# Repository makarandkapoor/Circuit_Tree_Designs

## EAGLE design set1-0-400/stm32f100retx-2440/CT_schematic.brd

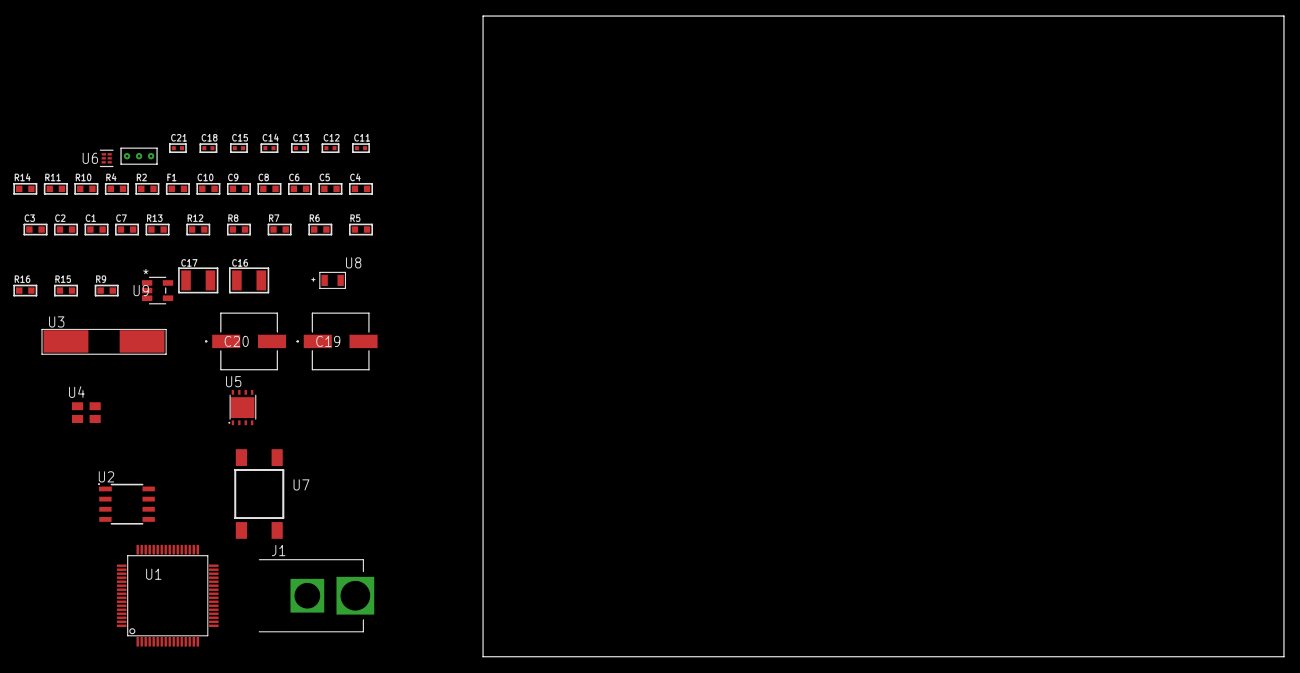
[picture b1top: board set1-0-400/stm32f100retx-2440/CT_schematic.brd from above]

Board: 2 copper layers, 100.0 x 80.0 mm, 47 parts (0 on the bottom side), 25 nets, no tracks yet.

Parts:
C1, C10: 1e-06; C0603
C2, C3, C4, C5, C6: 1e-07; C0603
C7: 4.7e-06; C0603
C8, C9: 1e-08; C0603
C11, C12: 1e-11; C0402
C13, C14, C15, C21: 1e-08; C0402
C16, C17: 1e-05; C1210
C18: 1e-07; C0402
C19, C20: 0.0001; EXV-9H
F1: 240.0; L0603
J1: PJ-037B; PJ-037B_PACKAGE
R2, R11: 1000.0; R0603
R4: 4700.0; R0603
R5, R6, R7, R8, R12, R13: 10000.0; R0603
R9: 100000.0; R0603
R10: 2231.0; R0603
R14: 9100.0; R0603
R15: 680000.0; R0603
R16: 120000.0; R0603
U1: stm32f100ret6; LQFP64
U2: AT25020B-SSHL-T; SOIC-8
U3: ABLS-25.000MHZ-B2F-T
U4: ASEK-32.768KHz-ECST; ASEK
U5: LP3878SDX-ADJ/NOPB; WSON-8
U6: TPS3895ADRYR; SON-6
U7: 4-1437565-2; SW_4-1437565-2
U8: Q65110A2395; LGM67K-G1J2-24-Z
U9: nc7sz125m5x; NC7SZ125M5X
U10: Dummy; DUMMY_PACKAGE_96

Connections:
CLK_CRYSTAL_U1_5: C11.1, U1.5, U3.1
CLK_CRYSTAL_U1_6: C12.1, U1.6, U3.2
CLK_U1_3: U1.3, U4.3
GND: C1.2, C2.2, C3.2, C4.2, C5.2, C6.2, C7.2, C8.2, C9.2, C10.2, C11.2, C12.2, C13.2, C14.2, C15.2, C16.2, C17.2, C18.2, C19.2, C20.2, C21.2, J1.2, R2.2, R5.2, R11.2, R14.2, R16.2, U1.12, U1.18, U1.31, U1.47, U1.63, U2.4, U4.2, U5.3, U5.PAD, U6.2, U8.C, U9.1, U9.3, U10.1
NET_U1_7: R4.1, U1.7, U9.4
NET_U1_13: C8.1, C9.1, C10.1, F1.1, U1.13
NET_U1_60: R5.1, U1.60
NET_U1_62: U7.3, U7.4
NET_U2_3: R6.1, U2.3
NET_U2_7: R8.1, U2.7
NET_U5_1: C15.1, U5.1
NET_U5_6: R10.2, R11.1, U5.6
NET_U5_8: R9.1, U5.8
NET_U6_1: R13.1, R14.1, U6.1
NET_U6_3: R15.2, R16.1, U6.3
NET_U6_4: R12.1, U6.4, U9.2
NET_U7_1: R2.1, U7.1, U7.2
PROC_ADC1_IN0: U1.14, U10.2
PROC_ADC1_IN1: U1.15, U10.3
PROC_SPI1_MISO: U1.22, U2.2
PROC_SPI1_MOSI: U1.23, U2.5
PROC_SPI1_NSS: R7.1, U1.20, U2.1
PROC_SPI1_SCK: U1.21, U2.6
VCC_S1_14V8: C16.1, C19.1, C20.1, J1.1, R9.2, U5.4
VCC_TIER1_3V3: C1.1, C2.1, C3.1, C4.1, C5.1, C6.1, C7.1, C13.1, C14.1, C17.1, C18.1, C21.1, F1.2, R4.2, R6.2, R7.2, R8.2, R10.1, R12.2, R13.2, R15.1, U1.1, U1.19, U1.32, U1.48, U1.64, U2.8, U4.4, U5.5, U6.6, U9.5

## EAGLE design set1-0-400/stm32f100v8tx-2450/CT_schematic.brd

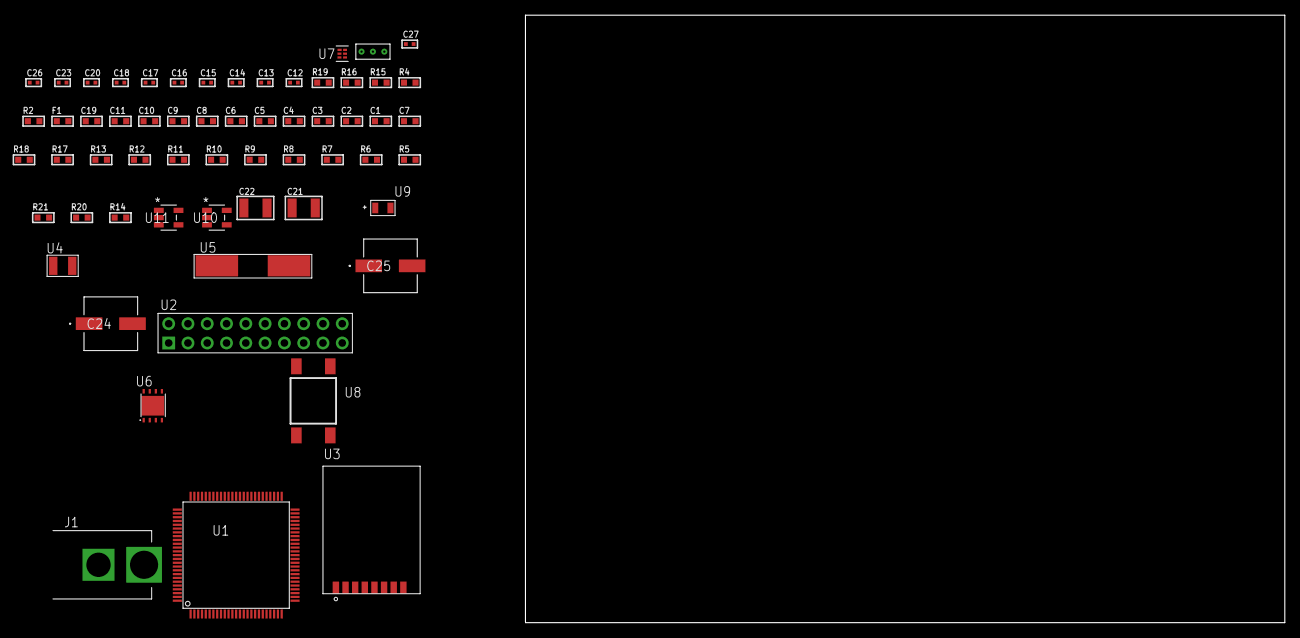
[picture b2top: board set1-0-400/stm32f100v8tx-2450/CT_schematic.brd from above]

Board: 2 copper layers, 100.0 x 80.0 mm, 60 parts (0 on the bottom side), 29 nets, no tracks yet.

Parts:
C1, C11, C19: 1e-06; C0603
C2, C3, C4, C5, C6, C8: 1e-07; C0603
C7: 4.7e-06; C0603
C9, C10: 1e-08; C0603
C12, C13, C14, C15: 1e-11; C0402
C16, C17, C18, C23: 1e-07; C0402
C20, C26, C27: 1e-08; C0402
C21, C22: 1e-05; C1210
C24, C25: 0.0001; EXV-9H
F1: 240.0; L0603
J1: PJ-037B; PJ-037B_PACKAGE
R2, R16: 1000.0; R0603
R4: 4700.0; R0603
R5, R6, R7, R8, R9, R10, R11, R12, R13, R17, R18: 10000.0; R0603
R14: 100000.0; R0603
R15: 2231.0; R0603
R19: 9100.0; R0603
R20: 680000.0; R0603
R21: 120000.0; R0603
U1: stm32f100v8t7; LQFP100
U2: TST-110-05-T-D-RA
U3: RFM75-S
U4: ABS07-32.768KHZ-7-T
U5: ABLS-25.000MHZ-B2F-T
U6: LP3878SDX-ADJ/NOPB; WSON-8
U7: TPS3895ADRYR; SON-6
U8: 4-1437565-2; SW_4-1437565-2
U9: Q65110A2395; LGM67K-G1J2-24-Z
U10, U11: nc7sz125m5x; NC7SZ125M5X
U12: Dummy; DUMMY_PACKAGE_125

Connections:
CLK_CRYSTAL_U1_8: C12.1, U1.8, U4.1
CLK_CRYSTAL_U1_9: C13.1, U1.9, U4.2
CLK_CRYSTAL_U1_12: C14.1, U1.12, U5.1
CLK_CRYSTAL_U1_13: C15.1, U1.13, U5.2
GND: C1.2, C2.2, C3.2, C4.2, C5.2, C6.2, C7.2, C8.2, C9.2, C10.2, C11.2, C12.2, C13.2, C14.2, C15.2, C16.2, C17.2, C18.2, C19.2, C20.2, C21.2, C22.2, C23.2, C24.2, C25.2, C26.2, C27.2, J1.2, R2.2, R5.2, R11.2, R16.2, R19.2, R21.2, U1.10, U1.19, U1.20, U1.27, U1.49, U1.74, U1.99, U2.4, U2.6, U2.8, U2.10, U2.12, U2.14, U2.16, U2.18, U2.20, U3.1, U6.3, U6.PAD, U7.2, U9.C, U10.2, U10.3, U11.1, U11.3, U12.1
NET_U1_14: R4.1, U1.14, U11.4
NET_U1_22: C9.1, C10.1, C11.1, F1.1, U1.21, U1.22
NET_U1_94: R5.1, U1.94
NET_U1_98: U8.3, U8.4
NET_U2_3: R6.1, U2.3
NET_U2_7: R8.1, U2.7
NET_U2_9: R9.1, U2.9
NET_U2_19: R11.1, U2.19
NET_U3_3: R12.1, U3.3
NET_U6_1: C20.1, U6.1
NET_U6_6: R15.2, R16.1, U6.6
NET_U6_8: R14.1, U6.8
NET_U7_1: R18.1, R19.1, U7.1
NET_U7_3: R20.2, R21.1, U7.3
NET_U7_4: R17.1, U7.4, U10.4, U11.2
NET_U8_1: R2.1, U8.1, U8.2
PROC_PE2: U1.1, U12.2
PROC_PE3: U1.2, U12.3
PROC_SPI1_NSS: R13.1, U3.4
PROC_SYS_JTDI: R7.1, U1.77, U2.5
PROC_SYS_JTDO_TRACESWO: U1.89, U2.13
RST_OUT_U2_SRESET_B: R10.1, U2.15, U10.1
VCC_S1_14V3: C21.1, C24.1, C25.1, J1.1, R14.2, U6.4
VCC_TIER1_3V3: C1.1, C2.1, C3.1, C4.1, C5.1, C6.1, C7.1, C8.1, C16.1, C17.1, C18.1, C19.1, C22.1, C23.1, C26.1, C27.1, F1.2, R4.2, R6.2, R7.2, R8.2, R9.2, R10.2, R12.2, R13.2, R15.1, R17.2, R18.2, R20.1, U1.6, U1.11, U1.28, U1.50, U1.75, U1.100, U2.1, U2.2, U3.2, U6.5, U7.6, U10.5, U11.5

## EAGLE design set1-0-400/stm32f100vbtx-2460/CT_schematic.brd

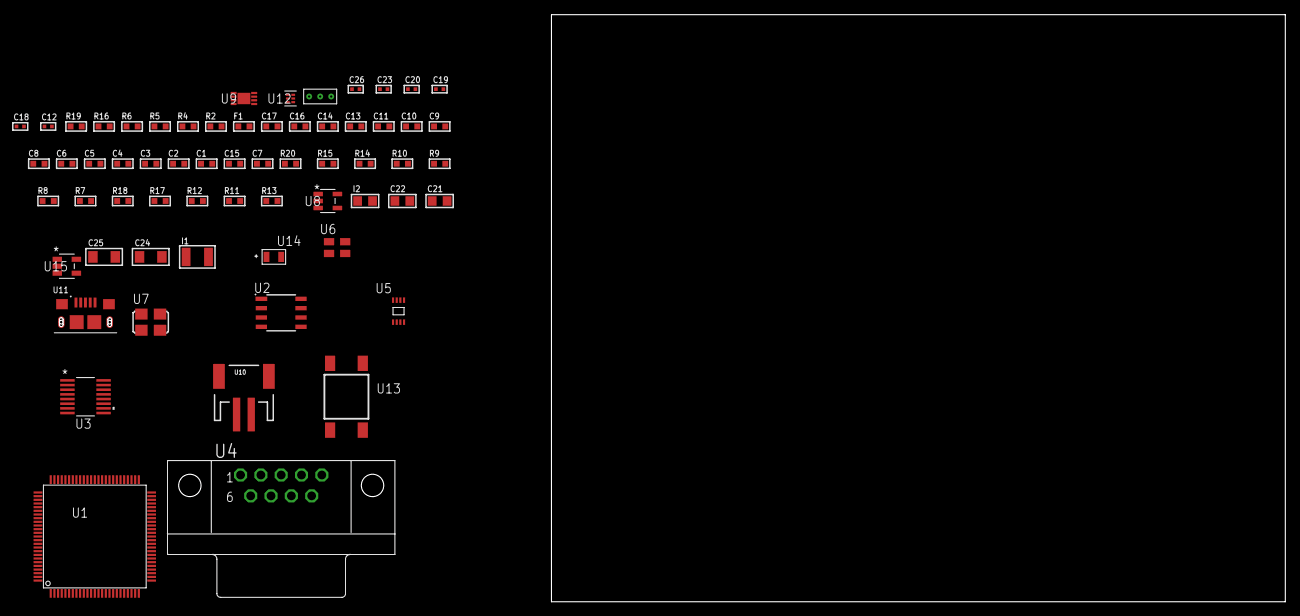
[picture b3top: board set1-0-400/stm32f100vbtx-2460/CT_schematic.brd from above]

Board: 2 copper layers, 167.1 x 80.0 mm, 63 parts (0 on the bottom side), 42 nets, no tracks yet.

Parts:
C1, C11, C13, C14, C16, C17: 1e-06; C0603
C2, C3, C4, C5, C6, C8: 1e-07; C0603
C7: 4.7e-06; C0603
C9, C10: 1e-08; C0603
C12, C18, C19, C20, C26: 1e-08; C0402
C15: 2.2e-07; C0603
C21, C22: 1e-05; C0805
C23: 1e-07; C0402
C24, C25: 1e-05; C1206
F1: 240.0; L0603
I1: 1e-05; L1210
I2: 2.2e-06; L0805
R2: 1000.0; R0603
R4: 4700.0; R0603
R5, R6: 2200.0; R0603
R7, R8, R9, R10, R14, R15, R20: 10000.0; R0603
R11: 100000.0; R0603
R12: 220000.0; R0603
R13: 1000000.0; R0603
R16: 9100.0; R0603
R17: 680000.0; R0603
R18: 120000.0; R0603
R19: 2000.0; R0603
U1: stm32f100vbt7; LQFP100
U2: AT25M02-SSHD-T; SOIC-8
U3: LTC2804CGN-1#PBF; SSOP-16
U4: 182-009-113R531; 182-009-MALE
U5: 24AA16-I/MC; TDFN-8/6MM
U6: ASEK-32.768KHz-ECST; ASEK
U7: ASFL1-25MHZ-NCS; ASFL1
U8: ltc3406es5; TSOT-23-5
U9: MCP73831T-2ACI/MC; DFN8_2X3MC
U10: S2B-PH-SM4-TB(LF)(SN); JST-2-SMD
U11: 10118193-0001LF; FCI_10118193-0001LF
U12: TPS3895ADRYR; SON-6
U13: 4-1437565-2; SW_4-1437565-2
U14: Q65110A2395; LGM67K-G1J2-24-Z
U15: nc7sz125m5x; NC7SZ125M5X
U16: Dummy; DUMMY_PACKAGE_140

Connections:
CLK_U1_8: U1.8, U6.3
CLK_U1_12: U1.12, U7.3
GND: C1.2, C2.2, C3.2, C4.2, C5.2, C6.2, C7.2, C8.2, C9.2, C10.2, C11.2, C12.2, C13.2, C14.2, C16.2, C17.2, C18.2, C19.2, C20.2, C21.2, C22.1, C22.2, C23.2, C24.2, C25.2, C26.2, R2.2, R7.2, R12.2, R16.2, R18.2, R19.2, U1.10, U1.19, U1.20, U1.27, U1.49, U1.74, U1.99, U2.4, U3.8, U4.5, U5.4, U6.2, U7.2, U8.2, U9.6, U9.9, U10.2, U11.5, U11.6, U11.7, U11.8, U11.9, U12.2, U14.C, U15.1, U15.3, U16.1
INPUT_USBPOWER_5V: C24.1, R20.2, U9.1, U9.2, U11.1
NET_U1_14: R4.1, U1.14, U15.4
NET_U1_22: C9.1, C10.1, C11.1, F1.1, U1.21, U1.22
NET_U1_92: R5.1, U1.92, U5.6
NET_U1_93: R6.1, U1.93, U5.5
NET_U1_94: R7.1, U1.94
NET_U1_98: U13.3, U13.4
NET_U2_3: R8.1, U2.3
NET_U2_7: R10.1, U2.7
NET_U3_6: C13.1, U3.6
NET_U3_7: C15.1, I1.2, U3.7
NET_U3_9: C14.1, U3.9
NET_U3_10: C15.2, U3.10
NET_U3_11: R11.1, U3.11
NET_U4_2: U3.1, U4.2
NET_U4_3: U3.3, U4.3
NET_U4_7: U3.2, U4.7
NET_U4_8: U3.4, U4.8
NET_U8_3: I2.1, U8.3
NET_U8_5: R12.1, R13.1, U8.5
NET_U8_ATNET_3: I2.2, R13.2
NET_U9_5: R20.1, U9.5
NET_U9_8: R19.1, U9.8
NET_U12_1: R15.1, R16.1, U12.1
NET_U12_3: R17.2, R18.1, U12.3
NET_U12_4: R14.1, U12.4, U15.2
NET_U13_1: R2.1, U13.1, U13.2
PROC_ADC1_IN0: U1.23, U16.2
PROC_ADC1_IN1: U1.24, U16.3
PROC_SPI1_MISO: U1.31, U2.2
PROC_SPI1_MOSI: U1.32, U2.5
PROC_SPI1_NSS: R9.1, U1.29, U2.1
PROC_SPI1_SCK: U1.30, U2.6
PROC_USART1_CTS: U1.70, U3.13
PROC_USART1_RTS: U1.71, U3.15
PROC_USART1_RX: U1.69, U3.16
PROC_USART1_TX: U1.68, U3.14
VCC_S1_3V7: C21.1, C25.1, U8.4, U9.3, U9.4, U10.1
VCC_TIER1_3V3: C1.1, C2.1, C3.1, C4.1, C5.1, C6.1, C7.1, C8.1, C12.1, C16.1, C17.1, C18.1, C19.1, C20.1, C22.2, C23.1, C26.1, F1.2, I1.1, I2.2, R4.2, R5.2, R6.2, R8.2, R9.2, R10.2, R11.2, R13.2, R14.2, R15.2, R17.1, U1.6, U1.11, U1.28, U1.50, U1.75, U1.100, U2.8, U3.5, U3.12, U5.7, U5.8, U6.4, U7.4, U12.6, U15.5

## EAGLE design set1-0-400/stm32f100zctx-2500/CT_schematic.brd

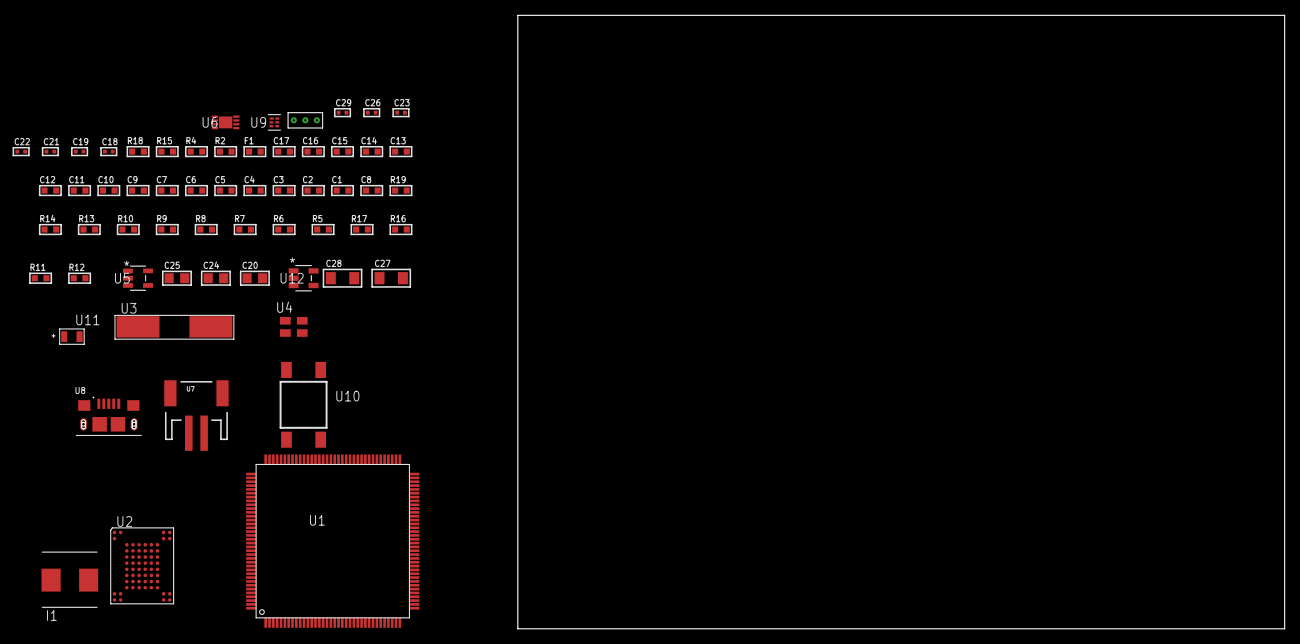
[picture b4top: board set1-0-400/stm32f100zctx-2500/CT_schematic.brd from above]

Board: 2 copper layers, 156.9 x 80.0 mm, 61 parts (0 on the bottom side), 35 nets, no tracks yet.

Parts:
C1, C17: 1e-06; C0603
C2, C3, C4, C5, C6, C7, C9, C10, C11, C12, C13, C14: 1e-07; C0603
C8: 4.7e-06; C0603
C15, C16: 1e-08; C0603
C18, C19: 1e-11; C0402
C20, C24, C25: 1e-05; C0805
C21, C22, C26: 1e-07; C0402
C23, C29: 1e-08; C0402
C27, C28: 1e-05; C1206
F1: 240.0; L0603
I1: 2e-06; WE-HCI_7030/7040/7050
R2: 1000.0; R0603
R4: 4700.0; R0603
R5, R6, R7, R8, R9, R10, R13, R14, R19: 10000.0; R0603
R11: 220000.0; R0603
R12: 1000000.0; R0603
R15: 9100.0; R0603
R16: 680000.0; R0603
R17: 120000.0; R0603
R18: 2000.0; R0603
U1: stm32f100zct7; LQFP144
U2: TH58NVG3S0HBAI4
U3: ABLS-25.000MHZ-B2F-T
U4: ASEK-32.768KHz-ECST; ASEK
U5: ltc3406es5; TSOT-23-5
U6: MCP73831T-2ACI/MC; DFN8_2X3MC
U7: S2B-PH-SM4-TB(LF)(SN); JST-2-SMD
U8: 10118193-0001LF; FCI_10118193-0001LF
U9: TPS3895ADRYR; SON-6
U10: 4-1437565-2; SW_4-1437565-2
U11: Q65110A2395; LGM67K-G1J2-24-Z
U12: nc7sz125m5x; NC7SZ125M5X
U13: Dummy; DUMMY_PACKAGE_128

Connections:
CLK_CRYSTAL_U1_23: C18.1, U1.23, U3.1
CLK_CRYSTAL_U1_24: C19.1, U1.24, U3.2
CLK_U1_8: U1.8, U4.3
GND: C1.2, C2.2, C3.2, C4.2, C5.2, C6.2, C7.2, C8.2, C9.2, C10.2, C11.2, C12.2, C13.2, C14.2, C15.2, C16.2, C17.2, C18.2, C19.2, C20.2, C21.2, C22.2, C23.2, C24.2, C25.1, C25.2, C26.2, C27.2, C28.2, C29.2, R2.2, R5.2, R11.2, R15.2, R17.2, R18.2, U1.16, U1.30, U1.31, U1.38, U1.51, U1.61, U1.71, U1.83, U1.94, U1.107, U1.120, U1.130, U1.143, U2.C5, U2.K3, U2.K8, U4.2, U5.2, U6.6, U6.9, U7.2, U8.5, U8.6, U8.7, U8.8, U8.9, U9.2, U11.C, U12.1, U12.3, U13.1
INPUT_USBPOWER_5V: C27.1, R19.2, U6.1, U6.2, U8.1
NET_U1_25: R4.1, U1.25, U12.4
NET_U1_33: C15.1, C16.1, C17.1, F1.1, U1.32, U1.33
NET_U1_138: R5.1, U1.138
NET_U1_142: U10.3, U10.4
NET_U2_C3: R9.1, U2.C3
NET_U2_C6: R6.1, U2.C6
NET_U2_C8: R10.1, U2.C8
NET_U5_3: I1.1, U5.3
NET_U5_5: R11.1, R12.1, U5.5
NET_U5_ATNET_3: I1.2, R12.2
NET_U6_5: R19.1, U6.5
NET_U6_8: R18.1, U6.8
NET_U9_1: R14.1, R15.1, U9.1
NET_U9_3: R16.2, R17.1, U9.3
NET_U9_4: R13.1, U9.4, U12.2
NET_U10_1: R2.1, U10.1, U10.2
PROC_ADC1_IN0: U1.34, U13.2
PROC_ADC1_IN1: U1.35, U13.3
PROC_FSMC_D0: U1.85, U2.H4
PROC_FSMC_D1: U1.86, U2.J4
PROC_FSMC_D2: U1.114, U2.K4
PROC_FSMC_D3: U1.115, U2.K5
PROC_FSMC_D4: U1.58, U2.K6
PROC_FSMC_D5: U1.59, U2.J7
PROC_FSMC_D6: U1.60, U2.K7
PROC_FSMC_D7: U1.63, U2.J8
PROC_FSMC_NOE: R7.1, U1.118, U2.D4
PROC_FSMC_NWE: R8.1, U1.119, U2.C7
VCC_S1_3V7: C24.1, C28.1, U5.4, U6.3, U6.4, U7.1
VCC_TIER1_3V3: C1.1, C2.1, C3.1, C4.1, C5.1, C6.1, C7.1, C8.1, C9.1, C10.1, C11.1, C12.1, C13.1, C14.1, C20.1, C21.1, C22.1, C23.1, C25.2, C26.1, C29.1, F1.2, I1.2, R4.2, R6.2, R7.2, R8.2, R9.2, R10.2, R12.2, R13.2, R14.2, R16.1, U1.6, U1.17, U1.39, U1.52, U1.62, U1.72, U1.84, U1.95, U1.108, U1.121, U1.131, U1.144, U2.H8, U2.J6, U4.4, U9.6, U12.5

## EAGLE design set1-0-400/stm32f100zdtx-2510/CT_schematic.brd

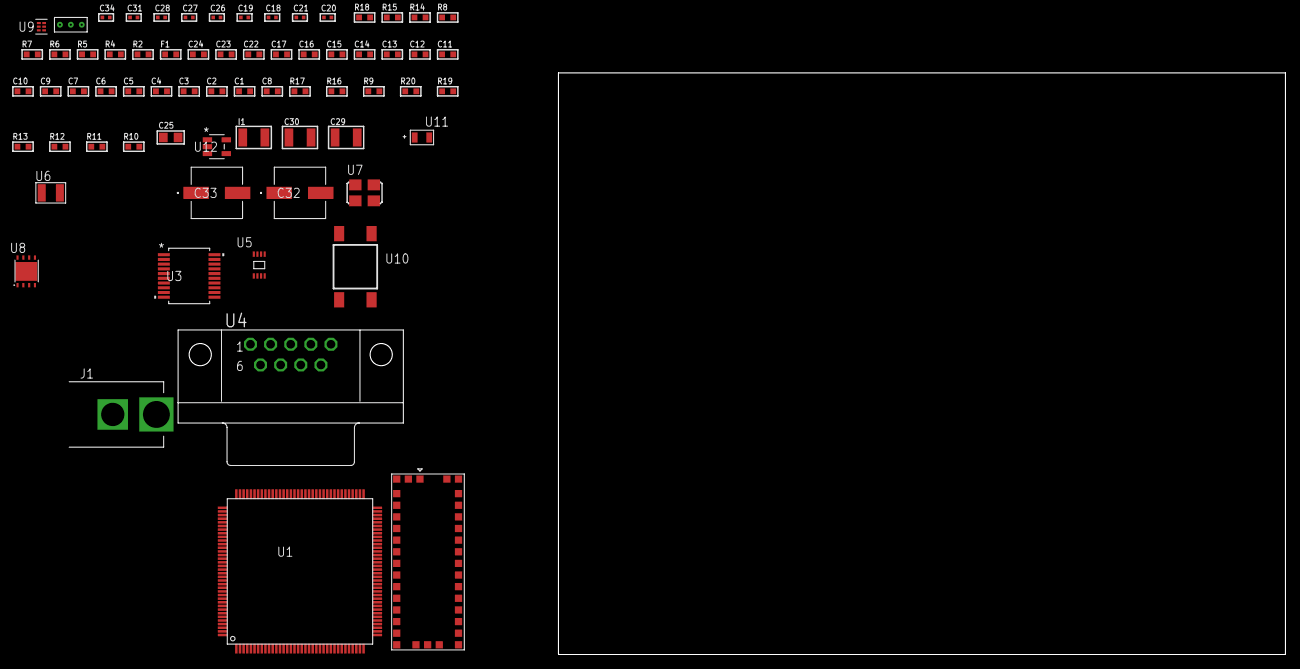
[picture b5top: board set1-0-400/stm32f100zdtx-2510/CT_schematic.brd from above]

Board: 2 copper layers, 100.0 x 80.0 mm, 68 parts (0 on the bottom side), 37 nets, no tracks yet.

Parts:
C1, C17, C22, C23, C24: 1e-06; C0603
C2, C3, C4, C5, C6, C7, C9, C10, C11, C12, C13, C14: 1e-07; C0603
C8: 4.7e-06; C0603
C15, C16: 1e-08; C0603
C18, C19: 1e-11; C0402
C20, C21: 2.2e-11; C0402
C25: 4.7e-06; C0805
C26, C27, C28, C34: 1e-08; C0402
C29, C30: 1e-05; C1210
C31: 1e-07; C0402
C32, C33: 0.0001; EXV-9H
F1: 240.0; L0603
I1: 1.5e-05; L1210
J1: PJ-037B; PJ-037B_PACKAGE
R2, R15: 1000.0; R0603
R4: 4700.0; R0603
R5, R6, R7, R8: 2200.0; R0603
R9, R16, R17: 10000.0; R0603
R10, R11, R12, R13: 100000.0; R0603
R14: 2231.0; R0603
R18: 9100.0; R0603
R19: 680000.0; R0603
R20: 120000.0; R0603
U1: stm32f100zdt7; LQFP144
U2: M10382
U3: MAX3218EAP+T; SSOP-20
U4: 182-009-113R531; 182-009-MALE
U5: 24AA16-I/MC; TDFN-8/6MM
U6: ABS07-32.768KHZ-7-T
U7: ASFL1-25MHZ-NCS; ASFL1
U8: LP3878SDX-ADJ/NOPB; WSON-8
U9: TPS3895ADRYR; SON-6
U10: 4-1437565-2; SW_4-1437565-2
U11: Q65110A2395; LGM67K-G1J2-24-Z
U12: nc7sz125m5x; NC7SZ125M5X
U13: Dummy; DUMMY_PACKAGE_145

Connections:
CLK_CRYSTAL_U1_8: C18.1, U1.8, U6.1
CLK_CRYSTAL_U1_9: C19.1, U1.9, U6.2
CLK_U1_23: U1.23, U7.3
GND: C1.2, C2.2, C3.2, C4.2, C5.2, C6.2, C7.2, C8.2, C9.2, C10.2, C11.2, C12.2, C13.2, C14.2, C15.2, C16.2, C17.2, C18.2, C19.2, C20.2, C21.2, C22.2, C23.2, C24.2, C26.2, C27.2, C28.2, C29.2, C30.2, C31.2, C32.2, C33.2, C34.2, J1.2, R2.2, R9.2, R15.2, R18.2, R20.2, U1.16, U1.30, U1.31, U1.38, U1.51, U1.61, U1.71, U1.83, U1.94, U1.107, U1.120, U1.130, U1.143, U2.2, U2.4, U2.14, U2.17, U2.21, U2.24, U2.26, U2.28, U2.33, U2.34, U2.35, U2.36, U3.5, U3.17, U3.20, U4.5, U5.4, U7.2, U8.3, U8.PAD, U9.2, U11.C, U12.1, U12.3, U13.1
NET_U1_25: R4.1, U1.25, U12.4
NET_U1_33: C15.1, C16.1, C17.1, F1.1, U1.32, U1.33
NET_U1_69: R7.1, U1.69, U5.6
NET_U1_70: R8.1, U1.70, U5.5
NET_U1_136: R5.1, U1.136, U2.19
NET_U1_137: R6.1, U1.137, U2.18
NET_U1_138: R9.1, U1.138
NET_U1_142: U10.3, U10.4
NET_U3_1: I1.1, U3.1
NET_U3_2: R10.1, U3.2
NET_U3_3: R11.1, U3.3
NET_U3_4: R12.1, U3.4
NET_U3_15: C24.1, U3.15
NET_U3_16: C25.2, U3.16
NET_U3_18: C25.1, U3.18
NET_U3_19: C23.1, U3.19
NET_U4_2: U3.12, U4.2
NET_U4_3: U3.14, U4.3
NET_U4_7: U3.11, U4.7
NET_U4_8: U3.13, U4.8
NET_U8_1: C28.1, U8.1
NET_U8_6: R14.2, R15.1, U8.6
NET_U8_8: R13.1, U8.8
NET_U9_1: R17.1, R18.1, U9.1
NET_U9_3: R19.2, R20.1, U9.3
NET_U9_4: R16.1, U9.4, U12.2
NET_U10_1: R2.1, U10.1, U10.2
PROC_ADC1_IN0: U1.34, U13.2
PROC_ADC1_IN1: U1.35, U13.3
PROC_UART4_RX: U1.112, U3.9
PROC_UART4_TX: U1.111, U3.7
VCC_S1_11V6: C29.1, C32.1, C33.1, J1.1, R13.2, U8.4
VCC_TIER1_3V3: C1.1, C2.1, C3.1, C4.1, C5.1, C6.1, C7.1, C8.1, C9.1, C10.1, C11.1, C12.1, C13.1, C14.1, C20.1, C21.1, C22.1, C26.1, C27.1, C30.1, C31.1, C34.1, F1.2, I1.2, R4.2, R5.2, R6.2, R7.2, R8.2, R10.2, R11.2, R12.2, R14.1, R16.2, R17.2, R19.1, U1.6, U1.17, U1.39, U1.52, U1.62, U1.72, U1.84, U1.95, U1.108, U1.121, U1.131, U1.144, U2.5, U2.25, U2.27, U3.6, U5.7, U5.8, U7.4, U8.5, U9.6, U12.5

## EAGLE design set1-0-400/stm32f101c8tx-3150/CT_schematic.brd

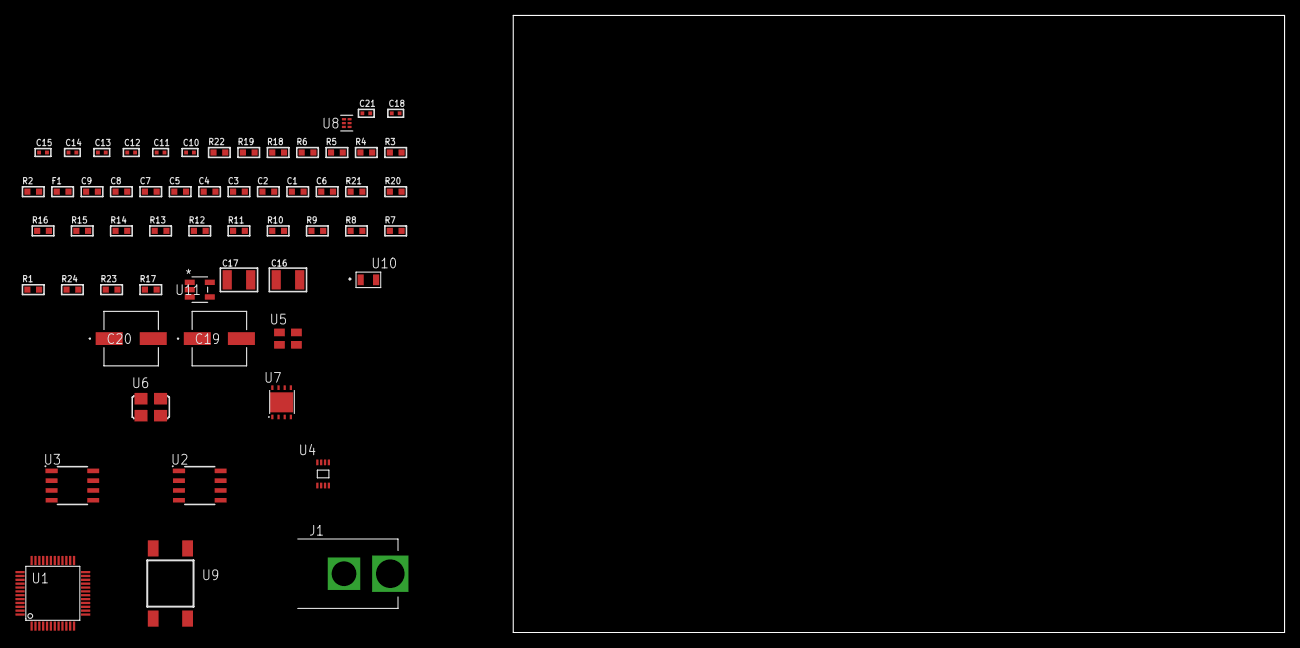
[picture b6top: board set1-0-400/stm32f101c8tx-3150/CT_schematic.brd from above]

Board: 2 copper layers, 100.0 x 80.0 mm, 58 parts (0 on the bottom side), 34 nets, no tracks yet.

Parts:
C1, C9: 1e-06; C0603
C2, C3, C4, C5: 1e-07; C0603
C6: 4.7e-06; C0603
C7, C8: 1e-08; C0603
C10, C11, C12, C13, C14, C15, C21: 1e-08; C0402
C16, C17: 1e-05; C1210
C18: 1e-07; C0402
C19, C20: 0.0001; EXV-9H
F1: 240.0; L0603
J1: PJ-037B; PJ-037B_PACKAGE
R1, R7, R8, R9, R10, R11, R12, R13, R14, R15, R16, R20, R21: 10000.0; R0603
R2, R19: 1000.0; R0603
R3: 1600.5; R0603
R4: 4700.0; R0603
R5, R6: 2200.0; R0603
R17: 100000.0; R0603
R18: 2231.0; R0603
R22: 9100.0; R0603
R23: 680000.0; R0603
R24: 120000.0; R0603
U1: STM32F101C8T6; LQFP48
U2: AT25080B-SSHL-T; SOIC-8
U3: AT25M01-SSHM-T; SOIC-8
U4: 24AA128T-I/MNY; TDFN-8/6MM
U5: ASEK-32.768KHz-ECST; ASEK
U6: ASFL1-25MHZ-NCS; ASFL1
U7: LP3878SDX-ADJ/NOPB; WSON-8
U8: TPS3895ADRYR; SON-6
U9: 4-1437565-2; SW_4-1437565-2
U10: Q65110A2395; LGM67K-G1J2-24-Z
U11: nc7sz125m5x; NC7SZ125M5X

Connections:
CLK_U1_3: U1.3, U5.3
CLK_U1_5: U1.5, U6.3
GND: C1.2, C2.2, C3.2, C4.2, C5.2, C6.2, C7.2, C8.2, C9.2, C10.2, C11.2, C12.2, C13.2, C14.2, C15.2, C16.2, C17.2, C18.2, C19.2, C20.2, C21.2, J1.2, R2.2, R7.2, R14.2, R16.2, R19.2, R22.2, R24.2, U1.8, U1.23, U1.35, U1.47, U2.4, U3.4, U4.4, U5.2, U6.2, U7.3, U7.PAD, U8.2, U10.C, U11.1, U11.3
NET_U1_7: R4.1, U1.7, U11.4
NET_U1_9: C7.1, C8.1, C9.1, F1.1, U1.9
NET_U1_42: R5.1, U1.42, U4.6
NET_U1_43: R6.1, U1.43, U4.5
NET_U1_44: R7.1, U1.44
NET_U1_45: R3.1, U1.45, U10.A
NET_U1_46: R1.1, U1.46, U9.3, U9.4
NET_U2_3: R8.1, U2.3
NET_U2_7: R10.1, U2.7
NET_U3_3: R11.1, U3.3
NET_U3_7: R13.1, U3.7
NET_U4_1: R14.1, U4.1
NET_U4_2: R15.1, U4.2
NET_U4_3: R16.1, U4.3
NET_U7_1: C15.1, U7.1
NET_U7_6: R18.2, R19.1, U7.6
NET_U7_8: R17.1, U7.8
NET_U8_1: R21.1, R22.1, U8.1
NET_U8_3: R23.2, R24.1, U8.3
NET_U8_4: R20.1, U8.4, U11.2
NET_U9_1: R2.1, U9.1, U9.2
PROC_SPI1_MISO: U1.16, U2.2
PROC_SPI1_MOSI: U1.17, U2.5
PROC_SPI1_NSS: R9.1, U1.14, U2.1
PROC_SPI1_SCK: U1.15, U2.6
PROC_SPI2_MISO: U1.27, U3.2
PROC_SPI2_MOSI: U1.28, U3.5
PROC_SPI2_NSS: R12.1, U1.25, U3.1
PROC_SPI2_SCK: U1.26, U3.6
VCC_S1_15V0: C16.1, C19.1, C20.1, J1.1, R17.2, U7.4
VCC_TIER1_3V3: C1.1, C2.1, C3.1, C4.1, C5.1, C6.1, C10.1, C11.1, C12.1, C13.1, C14.1, C17.1, C18.1, C21.1, F1.2, R1.2, R3.2, R4.2, R5.2, R6.2, R8.2, R9.2, R10.2, R11.2, R12.2, R13.2, R15.2, R18.1, R20.2, R21.2, R23.1, U1.1, U1.24, U1.36, U1.48, U2.8, U3.8, U4.7, U4.8, U5.4, U6.4, U7.5, U8.6, U11.5

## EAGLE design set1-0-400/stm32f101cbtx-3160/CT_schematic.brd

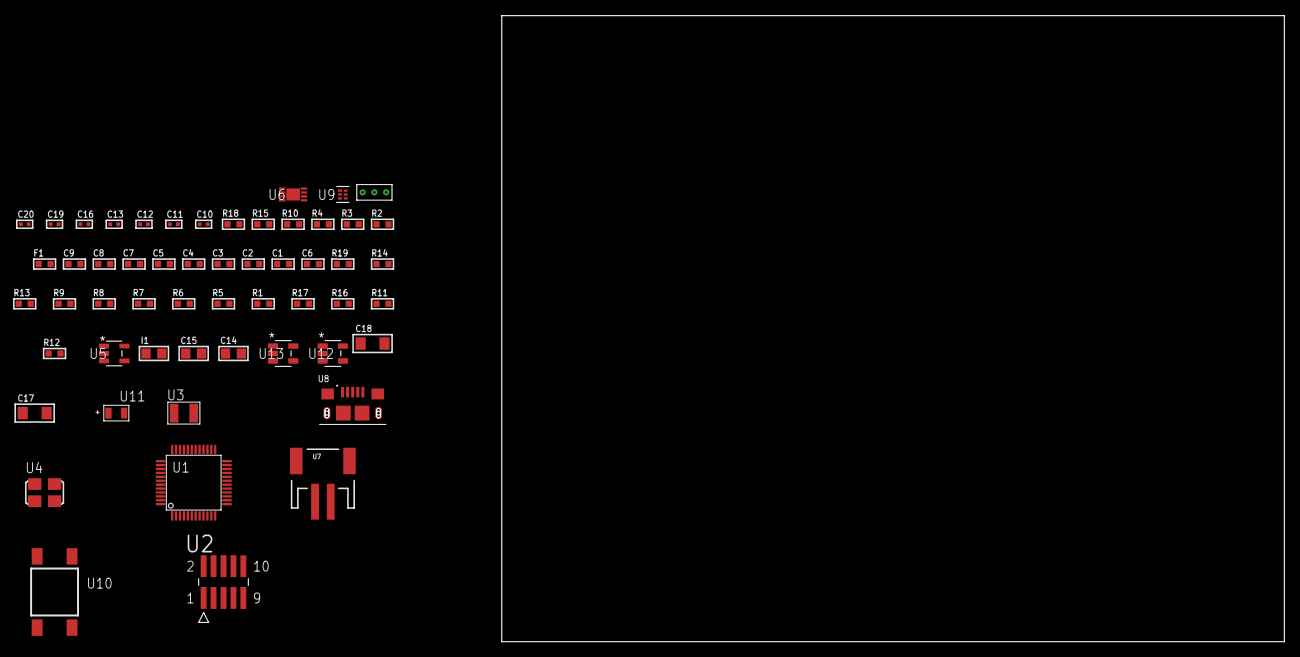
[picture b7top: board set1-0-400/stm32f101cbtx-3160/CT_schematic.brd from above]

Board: 2 copper layers, 122.6 x 80.0 mm, 55 parts (0 on the bottom side), 29 nets, no tracks yet.

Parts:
C1, C9: 1e-06; C0603
C2, C3, C4, C5: 1e-07; C0603
C6: 4.7e-06; C0603
C7, C8: 1e-08; C0603
C10, C11: 1e-11; C0402
C12, C16: 1e-07; C0402
C13, C19, C20: 1e-08; C0402
C14, C15: 1e-05; C0805
C17, C18: 1e-05; C1206
F1: 240.0; L0603
I1: 2.2e-06; L0805
R1, R5, R6, R7, R8, R9, R13, R14, R19: 10000.0; R0603
R2: 1000.0; R0603
R3: 1600.5; R0603
R4: 4700.0; R0603
R10: 5.0; R0603
R11: 220000.0; R0603
R12: 1000000.0; R0603
R15: 9100.0; R0603
R16: 680000.0; R0603
R17: 120000.0; R0603
R18: 2000.0; R0603
U1: STM32F101CBT6; LQFP48
U2: FTSH-105-01-L-DV-K; SAMTEC_FTSH-105-01-L-DV-K
U3: ABS07-32.768KHZ-7-T
U4: ASFL1-25MHZ-NCS; ASFL1
U5: ltc3406es5; TSOT-23-5
U6: MCP73831T-2ACI/MC; DFN8_2X3MC
U7: S2B-PH-SM4-TB(LF)(SN); JST-2-SMD
U8: 10118193-0001LF; FCI_10118193-0001LF
U9: TPS3895ADRYR; SON-6
U10: 4-1437565-2; SW_4-1437565-2
U11: Q65110A2395; LGM67K-G1J2-24-Z
U12, U13: nc7sz125m5x; NC7SZ125M5X
U14: Dummy; DUMMY_PACKAGE_113

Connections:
CLK_CRYSTAL_U1_3: C10.1, U1.3, U3.1
CLK_CRYSTAL_U1_4: C11.1, U1.4, U3.2
CLK_U1_5: U1.5, U4.3
GND: C1.2, C2.2, C3.2, C4.2, C5.2, C6.2, C7.2, C8.2, C9.2, C10.2, C11.2, C12.2, C13.2, C14.2, C15.1, C15.2, C16.2, C17.2, C18.2, C19.2, C20.2, R2.2, R5.2, R9.2, R10.2, R11.2, R15.2, R17.2, R18.2, U1.8, U1.23, U1.35, U1.47, U2.3, U2.5, U4.2, U5.2, U6.6, U6.9, U7.2, U8.5, U8.6, U8.7, U8.8, U8.9, U9.2, U11.C, U12.2, U12.3, U13.1, U13.3, U14.1
INPUT_USBPOWER_5V: C17.1, R19.2, U6.1, U6.2, U8.1
NET_U1_7: R4.1, U1.7, U13.4
NET_U1_9: C7.1, C8.1, C9.1, F1.1, U1.9
NET_U1_44: R5.1, U1.44
NET_U1_45: R3.1, U1.45, U11.A
NET_U1_46: R1.1, U1.46, U10.3, U10.4
NET_U2_2: R8.1, U2.2
NET_U2_4: R9.1, U2.4
NET_U2_9: R10.1, U2.9
NET_U5_3: I1.1, U5.3
NET_U5_5: R11.1, R12.1, U5.5
NET_U5_ATNET_3: I1.2, R12.2
NET_U6_5: R19.1, U6.5
NET_U6_8: R18.1, U6.8
NET_U9_1: R14.1, R15.1, U9.1
NET_U9_3: R16.2, R17.1, U9.3
NET_U9_4: R13.1, U9.4, U12.4, U13.2
NET_U10_1: R2.1, U10.1, U10.2
PROC_ADC1_IN3: U1.13, U14.3
PROC_ADC1_IN4: U1.14, U14.2
PROC_SYS_JTDI: R7.1, U1.38, U2.8
PROC_SYS_JTDO_TRACESWO: U1.39, U2.6
RST_OUT_U2_JTAG_RST_B: R6.1, U2.10, U12.1
VCC_S1_3V7: C14.1, C18.1, U5.4, U6.3, U6.4, U7.1
VCC_TIER1_3V3: C1.1, C2.1, C3.1, C4.1, C5.1, C6.1, C12.1, C13.1, C15.2, C16.1, C19.1, C20.1, F1.2, I1.2, R1.2, R3.2, R4.2, R6.2, R7.2, R8.2, R12.2, R13.2, R14.2, R16.1, U1.1, U1.24, U1.36, U1.48, U2.1, U4.4, U9.6, U12.5, U13.5

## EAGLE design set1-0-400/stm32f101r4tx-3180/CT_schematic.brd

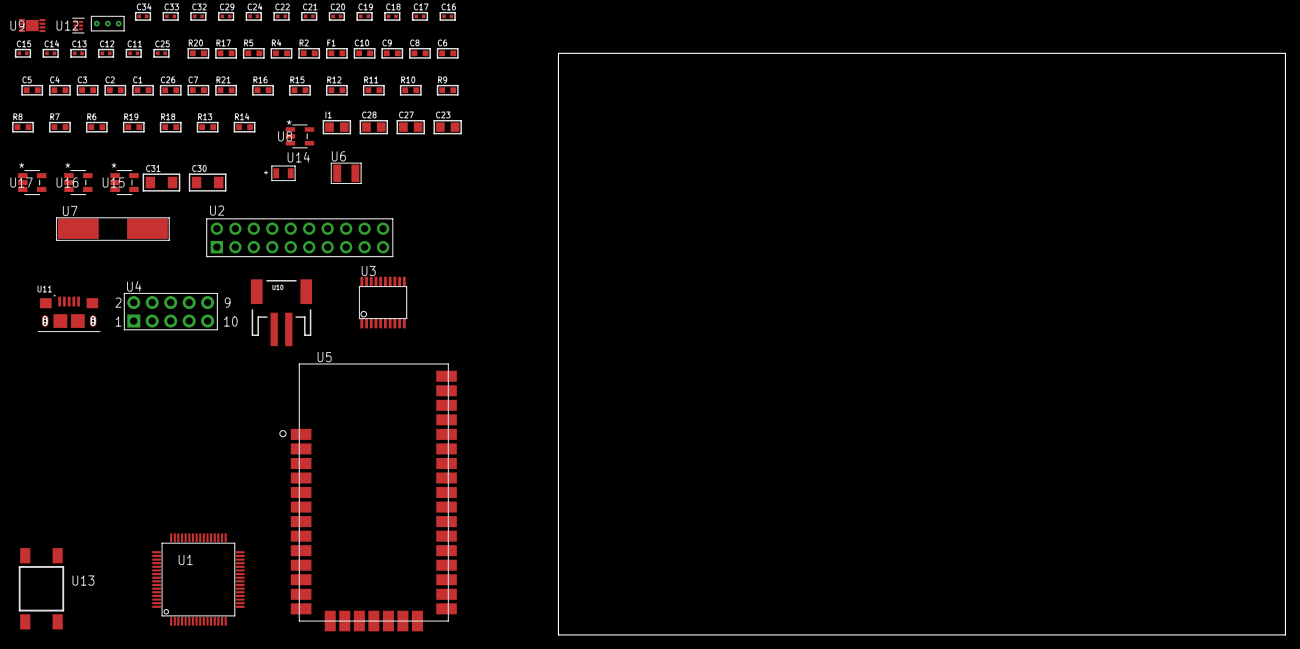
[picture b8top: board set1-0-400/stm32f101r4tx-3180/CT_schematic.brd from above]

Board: 2 copper layers, 73 parts (0 on the bottom side), 48 nets, no tracks yet.

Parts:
C1, C10: 1e-06; C0603
C2, C3, C4, C5, C6: 1e-07; C0603
C7: 4.7e-06; C0603
C8, C9: 1e-08; C0603
C11, C12, C13, C14: 1e-11; C0402
C15, C16, C17, C18, C19, C20, C21, C22, C24, C29: 1e-07; C0402
C23, C27, C28: 1e-05; C0805
C25: 4.7e-11; C0402
C26: 8.2e-12; C0603
C30, C31: 1e-05; C1206
C32, C33, C34: 1e-08; C0402
F1: 240.0; L0603
I1: 2.2e-06; L0805
R2: 1000.0; R0603
R4, R5: 4700.0; R0603
R6, R7, R8, R9, R10, R11, R12, R15, R16, R21: 10000.0; R0603
R13: 220000.0; R0603
R14: 1000000.0; R0603
R17: 9100.0; R0603
R18: 680000.0; R0603
R19: 120000.0; R0603
R20: 2000.0; R0603
U1: STM32F101R4T6; LQFP64
U2: TST-110-05-T-D-RA
U3: SP3203ECY-L/TR; TSSOP20-I
U4: HTSS-105-01-G-D
U5: XB24CZ7UIS-004
U6: ABS07-32.768KHZ-7-T
U7: ABLS-25.000MHZ-B2F-T
U8: ltc3406es5; TSOT-23-5
U9: MCP73831T-2ACI/MC; DFN8_2X3MC
U10: S2B-PH-SM4-TB(LF)(SN); JST-2-SMD
U11: 10118193-0001LF; FCI_10118193-0001LF
U12: TPS3895ADRYR; SON-6
U13: 4-1437565-2; SW_4-1437565-2
U14: Q65110A2395; LGM67K-G1J2-24-Z
U15, U16, U17: nc7sz125m5x; NC7SZ125M5X
U18: Dummy; DUMMY_PACKAGE_154

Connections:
CLK_CRYSTAL_U1_3: C11.1, U1.3, U6.1
CLK_CRYSTAL_U1_4: C12.1, U1.4, U6.2
CLK_CRYSTAL_U1_5: C13.1, U1.5, U7.1
CLK_CRYSTAL_U1_6: C14.1, U1.6, U7.2
GND: C1.2, C2.2, C3.2, C4.2, C5.2, C6.2, C7.2, C8.2, C9.2, C10.2, C11.2, C12.2, C13.2, C14.2, C15.2, C16.2, C17.2, C18.2, C21.2, C22.2, C23.2, C24.2, C25.2, C26.2, C27.2, C28.1, C28.2, C29.2, C30.2, C31.2, C32.2, C33.2, C34.2, R2.2, R6.2, R12.2, R13.2, R17.2, R19.2, R20.2, U1.12, U1.18, U1.31, U1.47, U1.63, U2.4, U2.6, U2.8, U2.10, U2.12, U2.14, U2.16, U2.18, U2.20, U3.18, U4.9, U5.1, U5.11, U5.13, U5.22, U5.35, U8.2, U9.6, U9.9, U10.2, U11.5, U11.6, U11.7, U11.8, U11.9, U12.2, U14.C, U15.2, U15.3, U16.1, U16.3, U17.1, U17.3, U18.1
INPUT_USBPOWER_5V: C30.1, R21.2, U9.1, U9.2, U11.1
NET_U1_7: R5.1, U1.7, U17.4
NET_U1_13: C8.1, C9.1, C10.1, F1.1, U1.13
NET_U1_60: R6.1, U1.60
NET_U1_62: U13.3, U13.4
NET_U2_3: R7.1, U2.3
NET_U2_7: R9.1, U2.7
NET_U2_9: R10.1, U2.9
NET_U2_19: R12.1, U2.19
NET_U3_1: C19.1, U3.1
NET_U3_2: C21.1, U3.2
NET_U3_3: C19.2, U3.3
NET_U3_4: C20.1, U3.4
NET_U3_5: C20.2, U3.5
NET_U3_6: C22.1, U3.6
NET_U4_3: U3.14, U4.3
NET_U4_4: U3.13, U4.4
NET_U4_5: U3.17, U4.5
NET_U4_6: U3.16, U4.6
NET_U5_6: R4.1, U5.6, U16.4
NET_U8_3: I1.1, U8.3
NET_U8_5: R13.1, R14.1, U8.5
NET_U8_ATNET_3: I1.2, R14.2
NET_U9_5: R21.1, U9.5
NET_U9_8: R20.1, U9.8
NET_U12_1: R16.1, R17.1, U12.1
NET_U12_3: R18.2, R19.1, U12.3
NET_U12_4: R15.1, U12.4, U15.4, U16.2, U17.2
NET_U13_1: R2.1, U13.1, U13.2
PROC_ADC1_IN2: U1.16, U18.3
PROC_ADC1_IN3: U1.17, U18.2
PROC_SPI1_MISO: U1.22, U5.17
PROC_SPI1_MOSI: U1.23, U5.16
PROC_SPI1_NSS: U1.20, U5.15
PROC_SPI1_SCK: U1.21, U5.14
PROC_SYS_JTDI: R8.1, U1.50, U2.5
PROC_SYS_JTDO_TRACESWO: U1.55, U2.13
PROC_USART1_CTS: U1.44, U3.8
PROC_USART1_RX: U1.43, U3.11
PROC_USART1_TX: U1.42, U3.7
RST_OUT_U2_SRESET_B: R11.1, U2.15, U15.1
VCC_S1_3V7: C27.1, C31.1, U8.4, U9.3, U9.4, U10.1
VCC_TIER1_3V3: C1.1, C2.1, C3.1, C4.1, C5.1, C6.1, C7.1, C15.1, C16.1, C17.1, C18.1, C23.1, C24.1, C25.1, C26.1, C28.2, C29.1, C32.1, C33.1, C34.1, F1.2, I1.2, R4.2, R5.2, R7.2, R8.2, R9.2, R10.2, R11.2, R14.2, R15.2, R16.2, R18.1, U1.1, U1.19, U1.32, U1.48, U1.64, U2.1, U2.2, U3.12, U3.19, U5.2, U5.27, U12.6, U15.5, U16.5, U17.5
